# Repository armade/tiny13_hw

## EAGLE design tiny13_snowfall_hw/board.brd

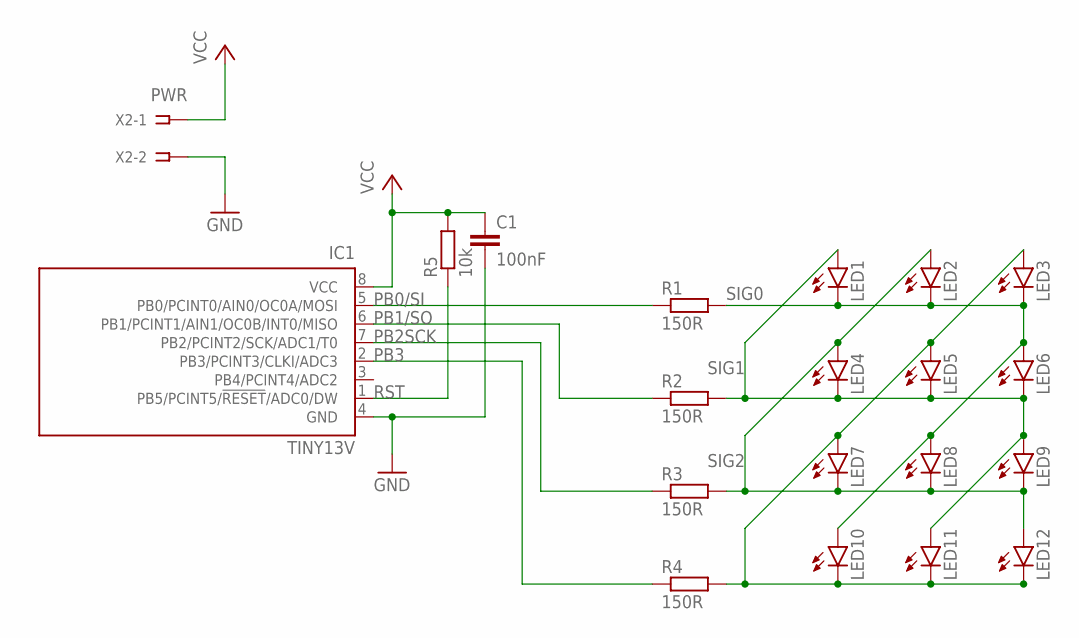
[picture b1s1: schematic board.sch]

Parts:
C1: 100nF; C1206K
IC1: TINY13V; 8S1
LED1, LED2, LED3, LED4, LED5, LED6, LED7, LED8, LED9, LED10, LED11, LED12: LEDSFH480; SFH480
R1, R2, R3, R4: 150R; R1206
R5: 10k; R1206
X2: PWR; SSW-101-02-G-D

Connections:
GND: C1.2, IC1.4 (GND), X2.2
PB0/SI: IC1.5 (PB0/PCINT0/AIN0/OC0A/MOSI), R1.1
PB1/SO: IC1.6 (PB1/PCINT1/AIN1/OC0B/INT0/MISO), R2.1
PB2SCK: IC1.7 (PB2/PCINT2/SCK/ADC1/T0), R3.1
PB3: IC1.2 (PB3/PCINT3/CLKI/ADC3), R4.1
RST: IC1.1 (PB5/PCINT5/!RESET!/ADC0/DW), R5.1
SIG0: LED1.K (C), LED2.K (C), LED3.K (C), LED6.A, LED8.A, LED10.A, R1.2
SIG1: LED1.A, LED4.K (C), LED5.K (C), LED6.K (C), LED9.A, LED11.A, R2.2
SIG2: LED2.A, LED4.A, LED7.K (C), LED8.K (C), LED9.K (C), LED12.A, R3.2
SIG3: LED3.A, LED5.A, LED7.A, LED10.K (C), LED11.K (C), LED12.K (C), R4.2
VCC: C1.1, IC1.8 (VCC), R5.2, X2.1

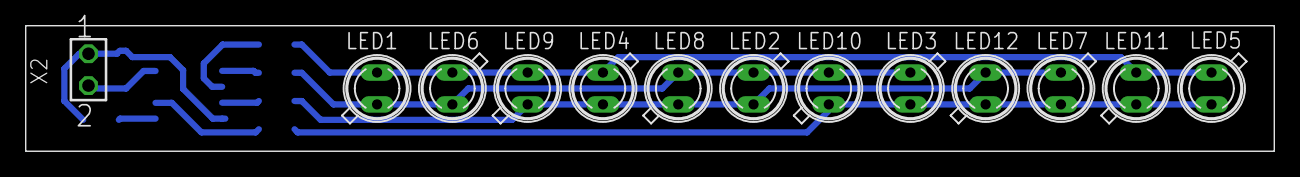
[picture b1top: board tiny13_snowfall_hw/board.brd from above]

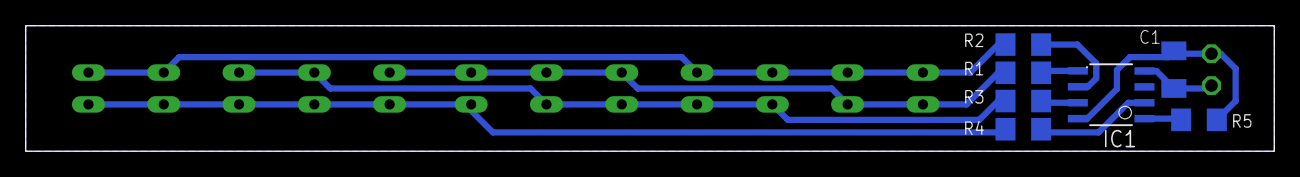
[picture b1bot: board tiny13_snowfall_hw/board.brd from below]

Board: 2 copper layers, 99.5 x 10.0 mm, 20 parts (7 on the bottom side), 11 nets.

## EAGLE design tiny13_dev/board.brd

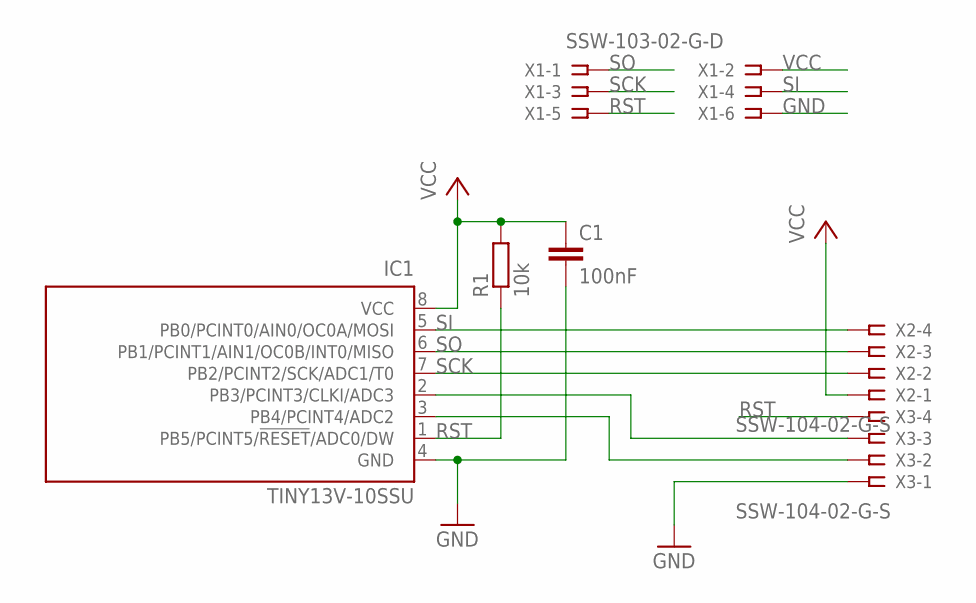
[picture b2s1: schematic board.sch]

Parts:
C1: 100nF; C1206K
IC1: TINY13V-10SSU; 8S1
R1: 10k; R1206
X1: SSW-103-02-G-D
X2, X3: SSW-104-02-G-S

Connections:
GND: C1.2, IC1.4 (GND), X1.6, X3.1
unnamed: IC1.3 (PB4/PCINT4/ADC2), X3.2
unnamed: IC1.2 (PB3/PCINT3/CLKI/ADC3), X3.3
RST: IC1.1 (PB5/PCINT5/!RESET!/ADC0/DW), R1.1, X1.5, X3.4
SCK: IC1.7 (PB2/PCINT2/SCK/ADC1/T0), X1.3, X2.2
SI: IC1.5 (PB0/PCINT0/AIN0/OC0A/MOSI), X1.4, X2.4
SO: IC1.6 (PB1/PCINT1/AIN1/OC0B/INT0/MISO), X1.1, X2.3
VCC: C1.1, IC1.8 (VCC), R1.2, X1.2, X2.1

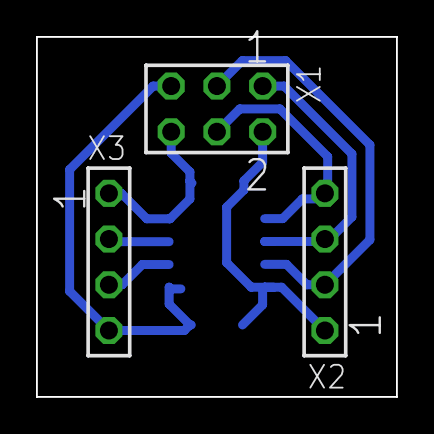
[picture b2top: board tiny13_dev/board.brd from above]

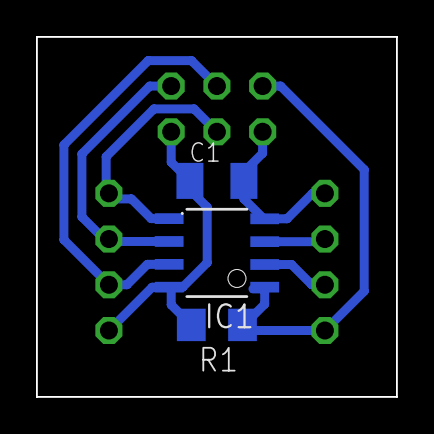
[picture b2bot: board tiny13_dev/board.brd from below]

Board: 2 copper layers, 20.0 x 20.0 mm, 6 parts (3 on the bottom side), 8 nets.

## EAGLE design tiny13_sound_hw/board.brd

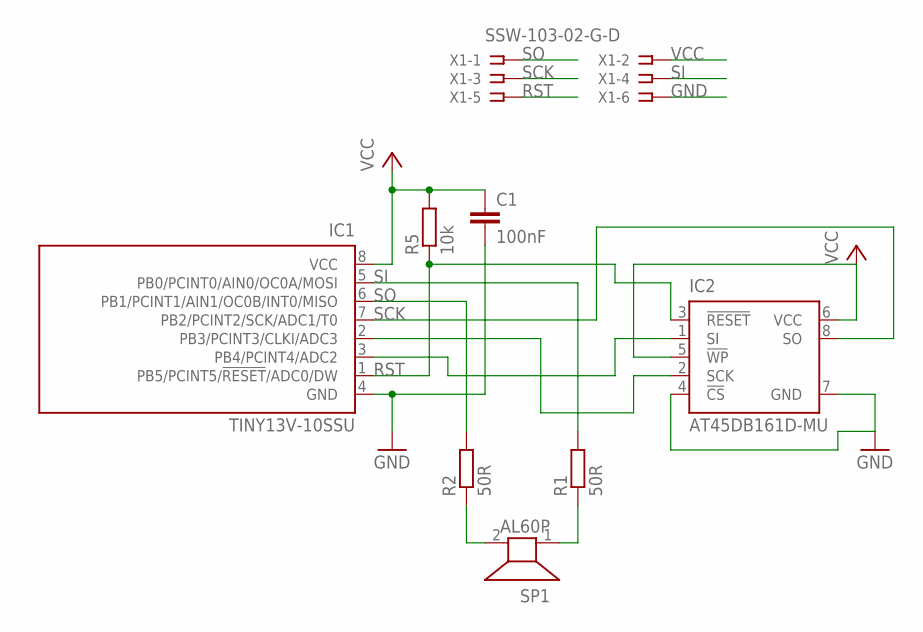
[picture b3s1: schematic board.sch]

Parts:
C1: 100nF; C1206K
IC1: TINY13V-10SSU; 8S1
IC2: AT45DB161D-MU; VDFN-8
R1, R2: 50R; 0204/5
R5: 10k; 0204/5
SP1: AL60P
X1: SSW-103-02-G-D

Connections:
GND: C1.2, IC1.4 (GND), IC2.4 (!CS), IC2.7 (GND), X1.6
unnamed: IC1.3 (PB4/PCINT4/ADC2), IC2.1 (SI)
unnamed: R1.1, SP1.1
unnamed: IC1.2 (PB3/PCINT3/CLKI/ADC3), IC2.2 (SCK)
unnamed: R2.1, SP1.2
RST: IC1.1 (PB5/PCINT5/!RESET!/ADC0/DW), IC2.3 (!RESET), R5.1, X1.5
SCK: IC1.7 (PB2/PCINT2/SCK/ADC1/T0), IC2.8 (SO), X1.3
SI: IC1.5 (PB0/PCINT0/AIN0/OC0A/MOSI), R1.2, X1.4
SO: IC1.6 (PB1/PCINT1/AIN1/OC0B/INT0/MISO), R2.2, X1.1
VCC: C1.1, IC1.8 (VCC), IC2.5 (!WP), IC2.6 (VCC), R5.2, X1.2

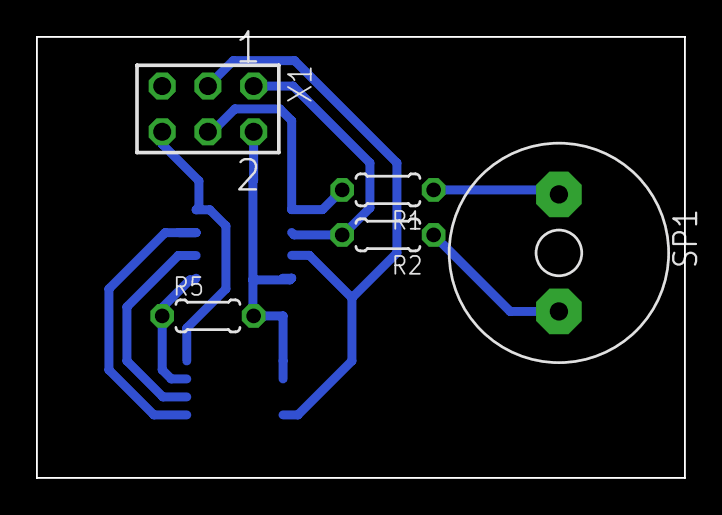
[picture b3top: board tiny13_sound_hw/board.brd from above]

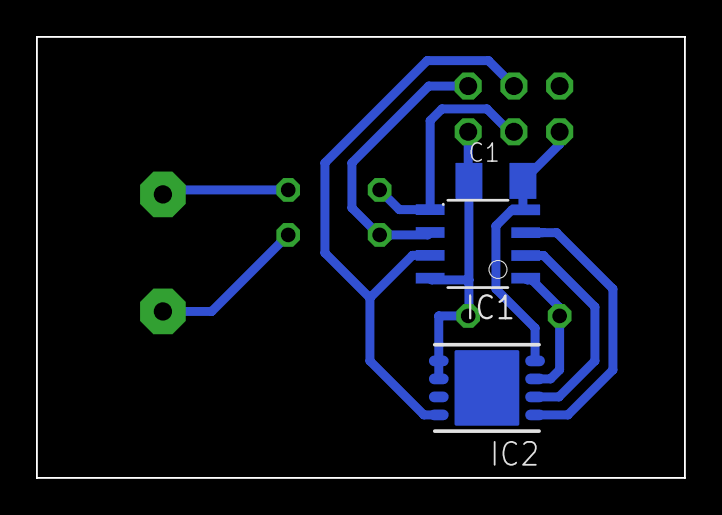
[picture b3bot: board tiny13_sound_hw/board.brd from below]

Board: 2 copper layers, 36.0 x 24.5 mm, 8 parts (3 on the bottom side), 10 nets.

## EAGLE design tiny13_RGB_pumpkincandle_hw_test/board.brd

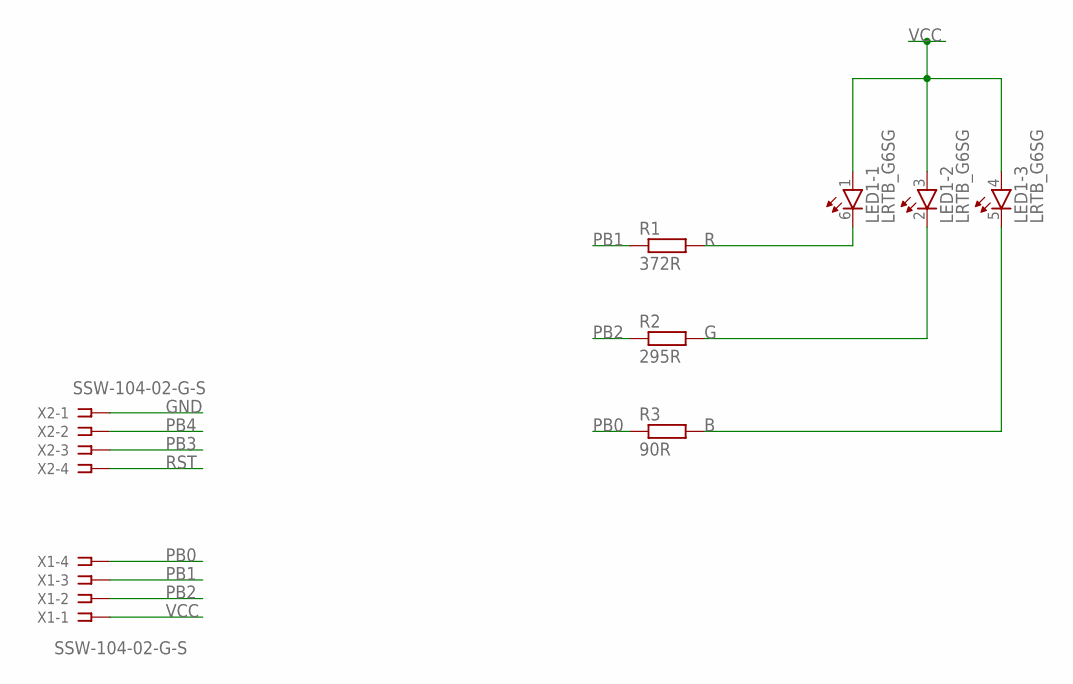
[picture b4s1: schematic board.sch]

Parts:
LED1: LRTB_G6SG
R1: 372R; R1206
R2: 295R; R1206
R3: 90R; R1206
X1, X2: SSW-104-02-G-S

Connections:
B: LED1.5 (C), R3.2
G: LED1.2 (C), R2.2
GND: X2.1
PB0: R3.1, X1.4
PB1: R1.1, X1.3
PB2: R2.1, X1.2
PB3: X2.3
PB4: X2.2
R: LED1.6 (C), R1.2
RST: X2.4
VCC: LED1.1 (A), LED1.3 (A), LED1.4 (A), X1.1

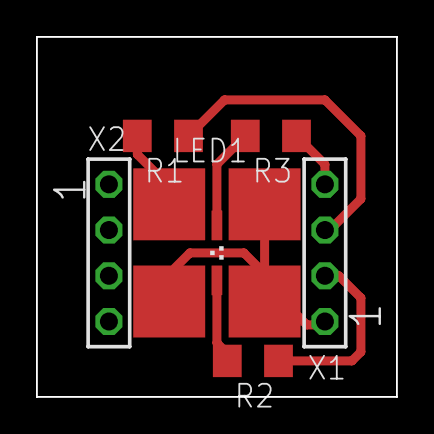
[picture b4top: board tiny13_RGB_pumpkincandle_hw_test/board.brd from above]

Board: 2 copper layers, 20.0 x 20.0 mm, 6 parts (0 on the bottom side), 7 nets.

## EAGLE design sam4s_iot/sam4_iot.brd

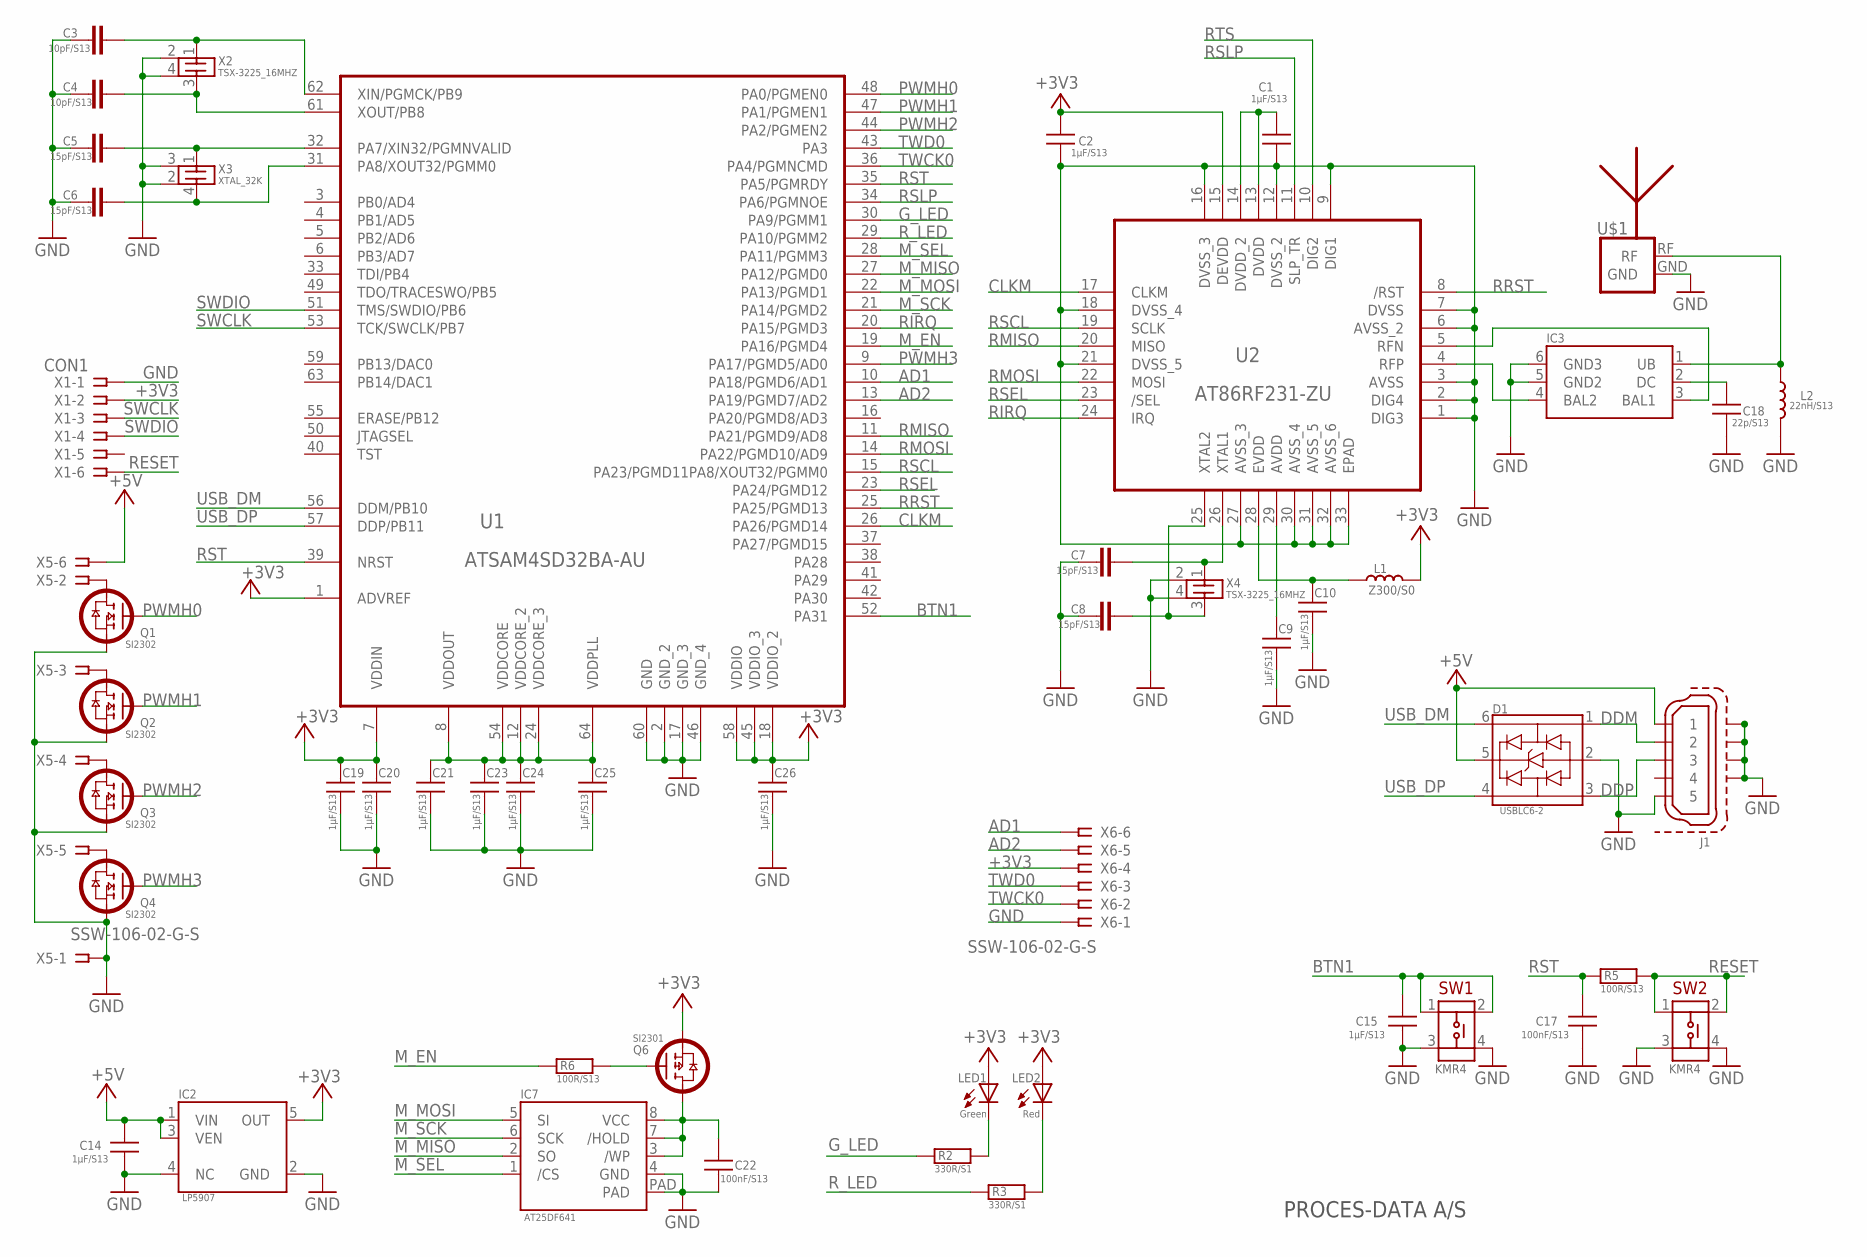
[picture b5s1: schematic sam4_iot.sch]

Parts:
C1, C2, C9, C10, C14, C15, C19, C20, C21, C23, C24, C25, C26: 1µF/S13; C0603
C3, C4: 10pF/S13; C0603
C5, C6, C7, C8: 15pF/S13; C0603
C17, C22: 100nF/S13; C0603
C18: 22p/S13; C0603
D1: USBLC6-2; SOT_6
IC2: LP5907; SOT23-5
IC3: BALUN; 2450BM15A0002
IC7: AT25DF641; VDFN_8MW1
J1: MICROUSB
L1: Z300/S0; L0603
L2: 22nH/S13; L0603
LED1: Green; OSRAM-MINI-TOP-LED
LED2: Red; OSRAM-MINI-TOP-LED
Q1, Q2, Q3, Q4: SI2302; TO-236(SOT23)
Q6: SI2301; TO-236(SOT23)
R2, R3: 330R/S1; R1206
R5, R6: 100R/S13; R0603
SW1, SW2: KMR4
U1: ATSAM4SD32BA-AU; QFP50P1200X1200X160-64N
U2: AT86RF231-ZU; QFN50P500X500X100-32N
U$1: ANTENNA_1RIGHT; SWRA117D_RIGHT
X1: CON1; SSW-103-02-S-D
X2, X4: TSX-3225_16MHZ; TSX-3225
X3: XTAL_32K; CM200S
X5, X6: SSW-106-02-G-S

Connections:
+3V3: C2.1, C19.1, C20.1, C26.1, IC2.5 (OUT), L1.P$1 (1), LED1.A, LED2.A, Q6.3 (S), U1.1 (ADVREF), U1.7 (VDDIN), U1.18 (VDDIO_2), U1.45 (VDDIO_3), U1.58 (VDDIO), U2.15 (DEVDD), X1.2, X6.4
+5V: C14.1, D1.5, IC2.1 (VIN), IC2.3 (VEN), J1.1, X5.6
AD1: U1.10 (PA18/PGMD6/AD1), X6.6
AD2: U1.13 (PA19/PGMD7/AD2), X6.5
BTN1: C15.1, SW1.1, SW1.2 (3), U1.52 (PA31)
CLKM: U1.26 (PA26/PGMD14), U2.17 (CLKM)
DDM: D1.1, J1.2
DDP: D1.3, J1.3
GND: C1.2, C2.2, C3.1, C4.1, C5.1, C6.1, C7.1, C8.1, C9.2, C10.2, C14.2, C15.2, C17.2, C18.2, C19.2, C20.2, C21.2, C22.2, C23.2, C24.2, C25.2, C26.2, D1.2, IC2.2 (GND), IC2.4 (NC), IC3.5 (GND2), IC3.6 (GND3), IC7.4 (GND), IC7.PAD, J1.5, J1.6, J1.7, J1.8, J1.9, L2.P$1 (1), Q1.2 (S), Q2.2 (S), Q3.2 (S), Q4.2 (S), SW1.3 (2), SW1.4, SW2.3 (2), SW2.4, U1.2 (GND_2), U1.17 (GND_3), U1.46 (GND_4), U1.60 (GND), U2.1 (DIG3), U2.2 (DIG4), U2.3 (AVSS), U2.6 (AVSS_2), U2.7 (DVSS), U2.9 (DIG1), U2.12 (DVSS_2), U2.16 (DVSS_3), U2.18 (DVSS_4), U2.21 (DVSS_5), U2.27 (AVSS_3), U2.30 (AVSS_4), U2.31 (AVSS_5), U2.32 (AVSS_6), U2.33 (EPAD), U$1.GND, X1.1, X2.2 (GND1), X2.4 (GND2), X3.2 (GND2), X3.3 (GND1), X4.2 (GND1), X4.4 (GND2), X5.1, X6.1
G_LED: R2.1, U1.30 (PA9/PGMM1)
M_EN: R6.1, U1.19 (PA16/PGMD4)
M_MISO: IC7.2 (SO), U1.27 (PA12/PGMD0)
M_MOSI: IC7.5 (SI), U1.22 (PA13/PGMD1)
M_SCK: IC7.6 (SCK), U1.21 (PA14/PGMD2)
M_SEL: IC7.1 (/CS), U1.28 (PA11/PGMM3)
unnamed: IC3.3 (BAL1), U2.5 (RFN)
unnamed: C9.1, U2.29 (AVDD)
unnamed: C21.1, C23.1, C24.1, C25.1, U1.8 (VDDOUT), U1.12 (VDDCORE_2), U1.24 (VDDCORE_3), U1.54 (VDDCORE), U1.64 (VDDPLL)
unnamed: C1.1, U2.13 (DVDD), U2.14 (DVDD_2)
unnamed: C10.1, L1.P$2 (2), U2.28 (EVDD)
unnamed: Q1.3 (D), X5.2
unnamed: Q2.3 (D), X5.3
unnamed: Q3.3 (D), X5.4
unnamed: Q4.3 (D), X5.5
unnamed: LED2.C, R3.2
unnamed: LED1.C, R2.2
unnamed: Q6.1 (G), R6.2
PWMH0: Q1.1 (G), U1.48 (PA0/PGMEN0)
PWMH1: Q2.1 (G), U1.47 (PA1/PGMEN1)
PWMH2: Q3.1 (G), U1.44 (PA2/PGMEN2)
PWMH3: Q4.1 (G), U1.9 (PA17/PGMD5/AD0)
RESET: R5.2, SW2.1, SW2.2 (3), X1.6
RF: IC3.1 (UB), L2.P$2 (2), U$1.RF
RFP: IC3.4 (BAL2), U2.4 (RFP)
RF_DC: C18.1, IC3.2 (DC)
RIRQ: U1.20 (PA15/PGMD3), U2.24 (IRQ)
RMISO: U1.11 (PA21/PGMD9/AD8), U2.20 (MISO)
RMOSI: U1.14 (PA22/PGMD10/AD9), U2.22 (MOSI)
RRST: U1.25 (PA25/PGMD13), U2.8 (/RST)
RSCL: U1.15 (PA23/PGMD11PA8/XOUT32/PGMM0), U2.19 (SCLK)
RSEL: U1.23 (PA24/PGMD12), U2.23 (/SEL)
RSLP: U1.34 (PA6/PGMNOE), U2.11 (SLP_TR)
RST: C17.1, R5.1, U1.35 (PA5/PGMRDY), U1.39 (NRST)
RTS: U2.10 (DIG2)
R_LED: R3.1, U1.29 (PA10/PGMM2)
SWCLK: U1.53 (TCK/SWCLK/PB7), X1.3
SWDIO: U1.51 (TMS/SWDIO/PB6), X1.4
TWCK0: U1.36 (PA4/PGMNCMD), X6.2
TWD0: U1.43 (PA3), X6.3
USB_DM: D1.6, U1.56 (DDM/PB10)
USB_DP: D1.4, U1.57 (DDP/PB11)
VCCF: C22.1, IC7.3 (/WP), IC7.7 (/HOLD), IC7.8 (VCC), Q6.2 (D)
XTAL1: C4.2, U1.61 (XOUT/PB8), X2.3 (X2)
XTAL2: C3.2, U1.62 (XIN/PGMCK/PB9), X2.1 (X1)
XTAL3: C7.2, U2.26 (XTAL1), X4.1 (X1)
XTAL4: C8.2, U2.25 (XTAL2), X4.3 (X2)
XTAL32KHZ1: C6.2, U1.31 (PA8/XOUT32/PGMM0), X3.4 (X2)
XTAL32KHZ2: C5.2, U1.32 (PA7/XIN32/PGMNVALID), X3.1 (X1)

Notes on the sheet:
PROCES-DATA A/S

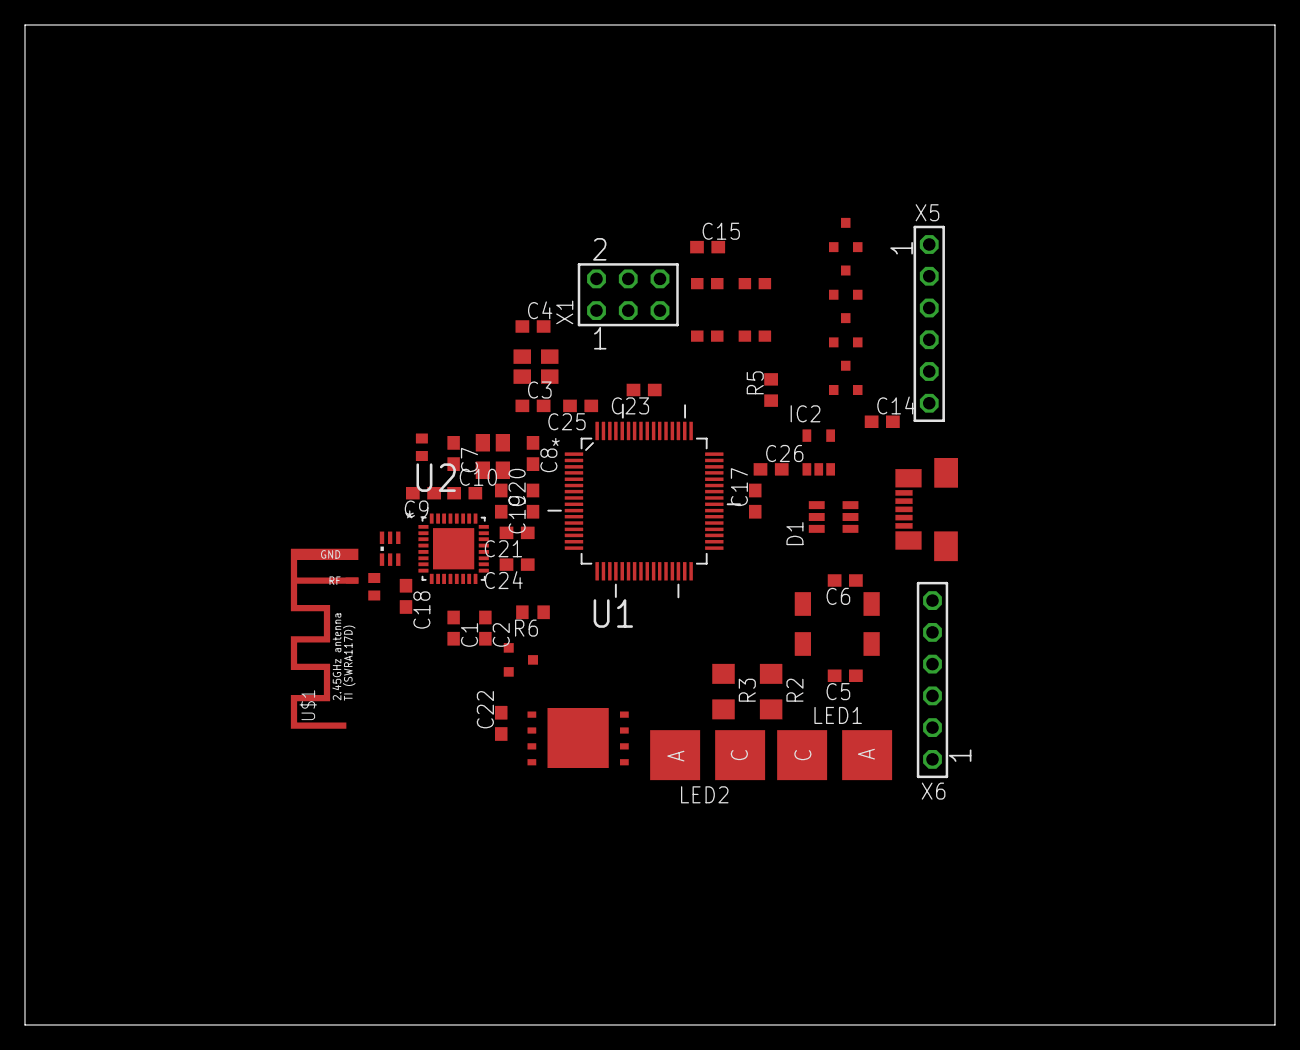
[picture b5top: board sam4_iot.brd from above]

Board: 2 copper layers, 100.0 x 80.0 mm, 51 parts (0 on the bottom side), 57 nets.

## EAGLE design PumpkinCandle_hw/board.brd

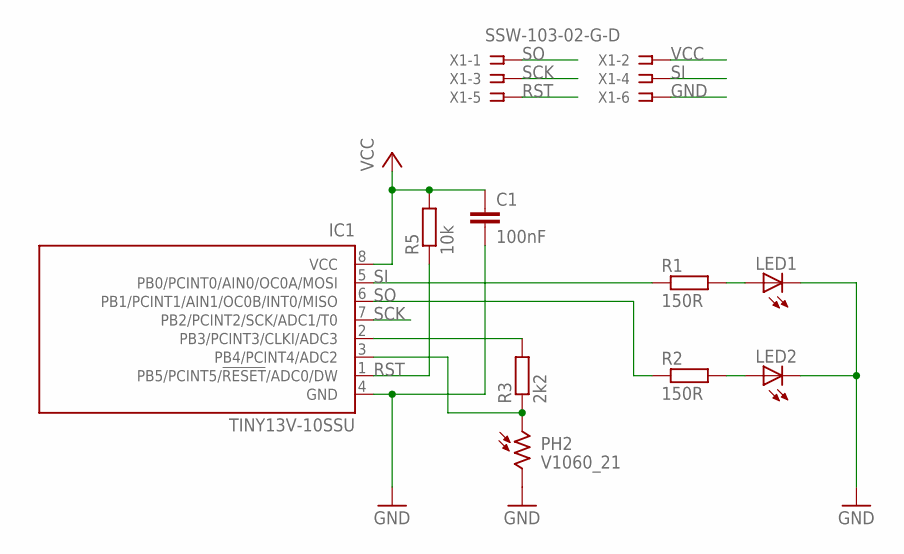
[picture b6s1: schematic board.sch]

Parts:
C1: 100nF; C1206K
IC1: TINY13V-10SSU; 8S1
LED1, LED2: LED_ESML0603; LED_SML0603
PH2: V1060_21; TO-5_V10
R1, R2: 150R; 0204/5
R3: 2k2; 0204/5
R5: 10k; 0204/5
X1: SSW-103-02-G-D

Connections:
GND: C1.2, IC1.4 (GND), LED1.C, LED2.C, PH2.2, X1.6
unnamed: IC1.3 (PB4/PCINT4/ADC2), PH2.1, R3.1
unnamed: LED2.A, R2.2
unnamed: LED1.A, R1.2
unnamed: IC1.2 (PB3/PCINT3/CLKI/ADC3), R3.2
RST: IC1.1 (PB5/PCINT5/!RESET!/ADC0/DW), R5.1, X1.5
SCK: IC1.7 (PB2/PCINT2/SCK/ADC1/T0), X1.3
SI: IC1.5 (PB0/PCINT0/AIN0/OC0A/MOSI), R1.1, X1.4
SO: IC1.6 (PB1/PCINT1/AIN1/OC0B/INT0/MISO), R2.1, X1.1
VCC: C1.1, IC1.8 (VCC), R5.2, X1.2

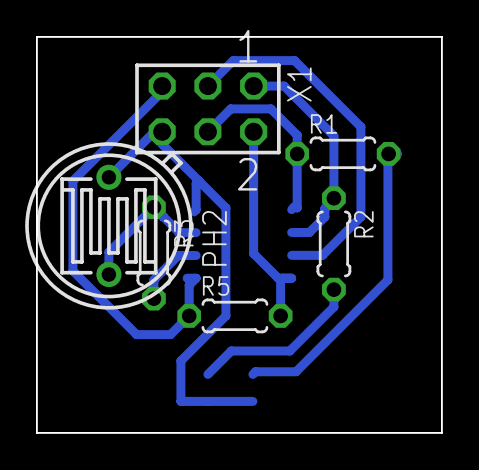
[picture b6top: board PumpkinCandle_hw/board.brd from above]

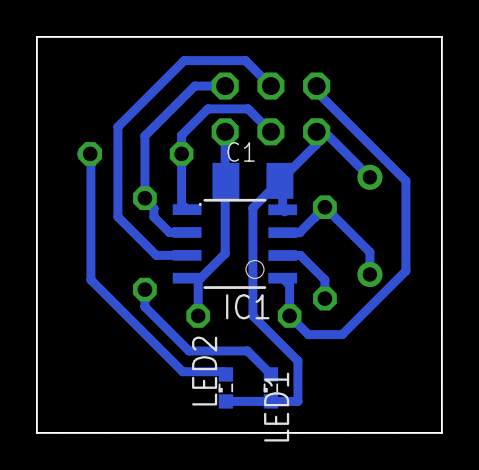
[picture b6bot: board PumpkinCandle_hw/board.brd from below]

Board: 2 copper layers, 22.5 x 22.0 mm, 10 parts (4 on the bottom side), 10 nets.

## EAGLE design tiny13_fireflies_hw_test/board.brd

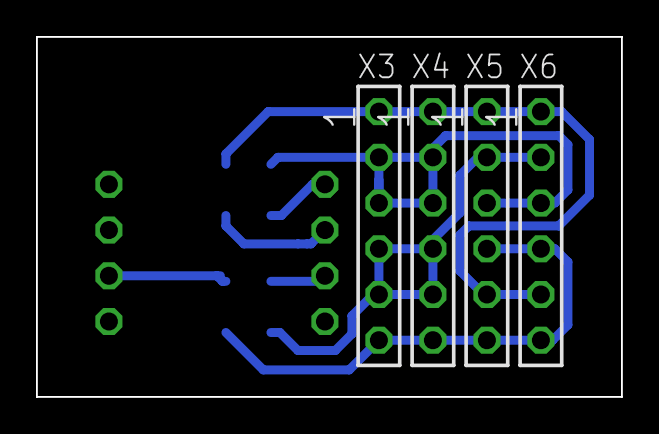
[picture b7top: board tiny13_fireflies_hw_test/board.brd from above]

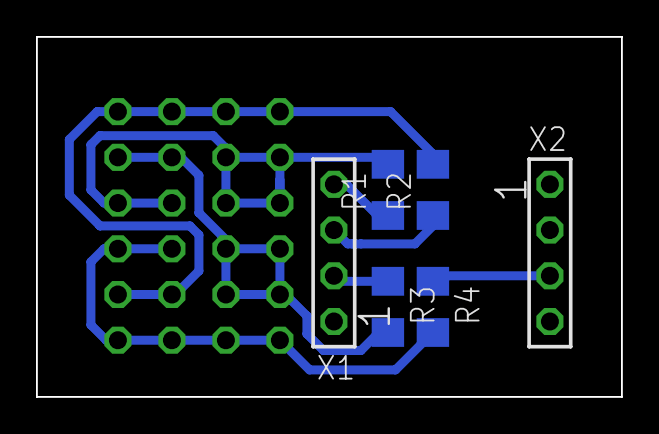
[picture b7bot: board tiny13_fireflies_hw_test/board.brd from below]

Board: 2 copper layers, 32.5 x 20.0 mm, 10 parts (6 on the bottom side), 8 nets.

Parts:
R1, R2, R3, R4: 50R; R1206
X1, X2: SSW-104-02-G-S
X3, X4, X5, X6: SSW-106-02-G-S

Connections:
PB0: R1.1, X1.4
PB1: R2.1, X1.3
PB2: R3.1, X1.2
PB3: R4.1, X2.3
SIG0: R1.2, X3.2, X3.3, X4.2, X4.3, X5.3, X6.3
SIG1: R2.2, X3.1, X4.1, X5.1, X5.5, X6.1, X6.5
SIG2: R3.2, X3.4, X3.5, X4.4, X4.5, X5.2, X6.2
SIG3: R4.2, X3.6, X4.6, X5.4, X5.6, X6.4, X6.6

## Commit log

2019-10-28 initial
2019-10-30 optimized snowfall hw
